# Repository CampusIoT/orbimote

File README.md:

# OrbiMote: open-sourced LoRaWAN high-altitude balloon (HAB) tracker

"urbi et orbi" : to the city and the world

The Orbimote is a LoRa/LoRaWAN endpoint
* for tracking sounding balloons
* and for implementing flying repeaters and flying field testers.

# HW & FW
* [Hardware](./hardware)
* [Firmware](./firmware)

## GNSS additional modules for near-space applications

According [CoCom](https://en.wikipedia.org/wiki/CoCom) regulations, most of commercial GPS modules stop at altitudes higher than 18000 meters and for speeds higher than 1000 knots (1852 km/h).

Here is a list of GPS modules : [gnss_modules.md](./gnss_modules.md)

## Barometers for near-space applications

Here is a list of barometer components and modules : [barometers.md](./barometers.md)

## Flights

[High-altitude flights](https://gricad-gitlab.univ-grenoble-alpes.fr/thingsat/public/-/blob/master/balloons)

### 2019
Valence, May 2019. [more](https://gricad-gitlab.univ-grenoble-alpes.fr/thingsat/public/-/blob/master/balloons/2019-05-09/README.md)

Legend: The balloon track (in red), Orange Liveobject stations (in orange), TTN stations (in grey)
### 2020
Aire-sur-l'Adour, September 2020. [more](https://gricad-gitlab.univ-grenoble-alpes.fr/thingsat/public/-/blob/master/balloons/2020-09-23/README.md)

Legend: The balloon track (in green for departure, blue line and red for arrival), Orange Liveobject stations (in blue)

### 2021
Aire-sur-l'Adour, April 2021. [more](https://gricad-gitlab.univ-grenoble-alpes.fr/thingsat/public/-/blob/master/balloons/2021-04-15/README.md)

Legend: The 3 balloons tracks (in green for departure, red for arrival), Orange Liveobject stations in orange, Requea stations in blue, Swisscom (thru Actility) in red.

## Altenatives
* [HAB2 High Altitude Balloon Tracker RFM9x](https://github.com/StuartsProjects/HAB2)

## Other usages
* Runners trackers
* Meshed-network of trail runners/trekers

## License
TBD

## Authors
* Didier DONSEZ
* Vivien QUEMA
* Gregory NOCERA

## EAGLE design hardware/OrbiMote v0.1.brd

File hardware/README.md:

# OrbiMote :: Hardware  

## Schematics   
* Done with [Eagle 7.7 Express](https://www.autodesk.com/products/eagle/free-download).

## Bill of material

* IMST iM880A
  * MCU: STM32L151CB - 128K FLASH, 10K RAM, Timers, SPI, I2C, USART, USB 2.0 full-speed device/host/OTG controller,DAC, ADC, DMA
  * RADIO: SX1272
* or [IMST iM880B-L](https://wireless-solutions.de/products/radiomodules/im880b-l.html)
* or [IMST iM881A-M](https://wireless-solutions.de/products/long-range-radio/im881a.html)
* MPL3115 : temperature, pressure
* MMA8451 : accelormeter
* MAG3110 : magnetometer
* reed switch
* button
* power switch
* SMA and UFL antenna connectors
* CR2032 battery holder
* plug for AA lithium battery
* pin header for JTAG/SWD
* pin header for RXTX

## Header for JTAG/SWD
Noted as JP1

    Pin 1 : GND
    Pin 2 : VCC
    Pin 3 : JTCK/SWCLK (pin 2 of the iM880a)
    Pin 4 : JTMS/SWDAT (pin 3 of the iM880a)
    Pin 5 : JTDO       (pin 4 of the iM880a)
    Pin 6 : JTDI       (pin 5 of the iM880a)
    Pin 7 : RESET      (pin 7 of the iM880a)

## Header for RXTX
Noted as JP2

    Pin 1 : GND
    Pin 2 : RX
    Pin 3 : TX

## GNSS additional modules for near-space applications

According [CoCom](https://en.wikipedia.org/wiki/CoCom) regulations, most of commercial GPS modules stop at altitudes higher than 18000 meters and for speeds higher than 1000 knots (1852 km/h).

Here is a list of GPS modules : [gnss_modules.md](../gnss_modules.md)

## Barometers for near-space applications

Here is a list of barometer components and modules : [barometers.md](../barometers.md)

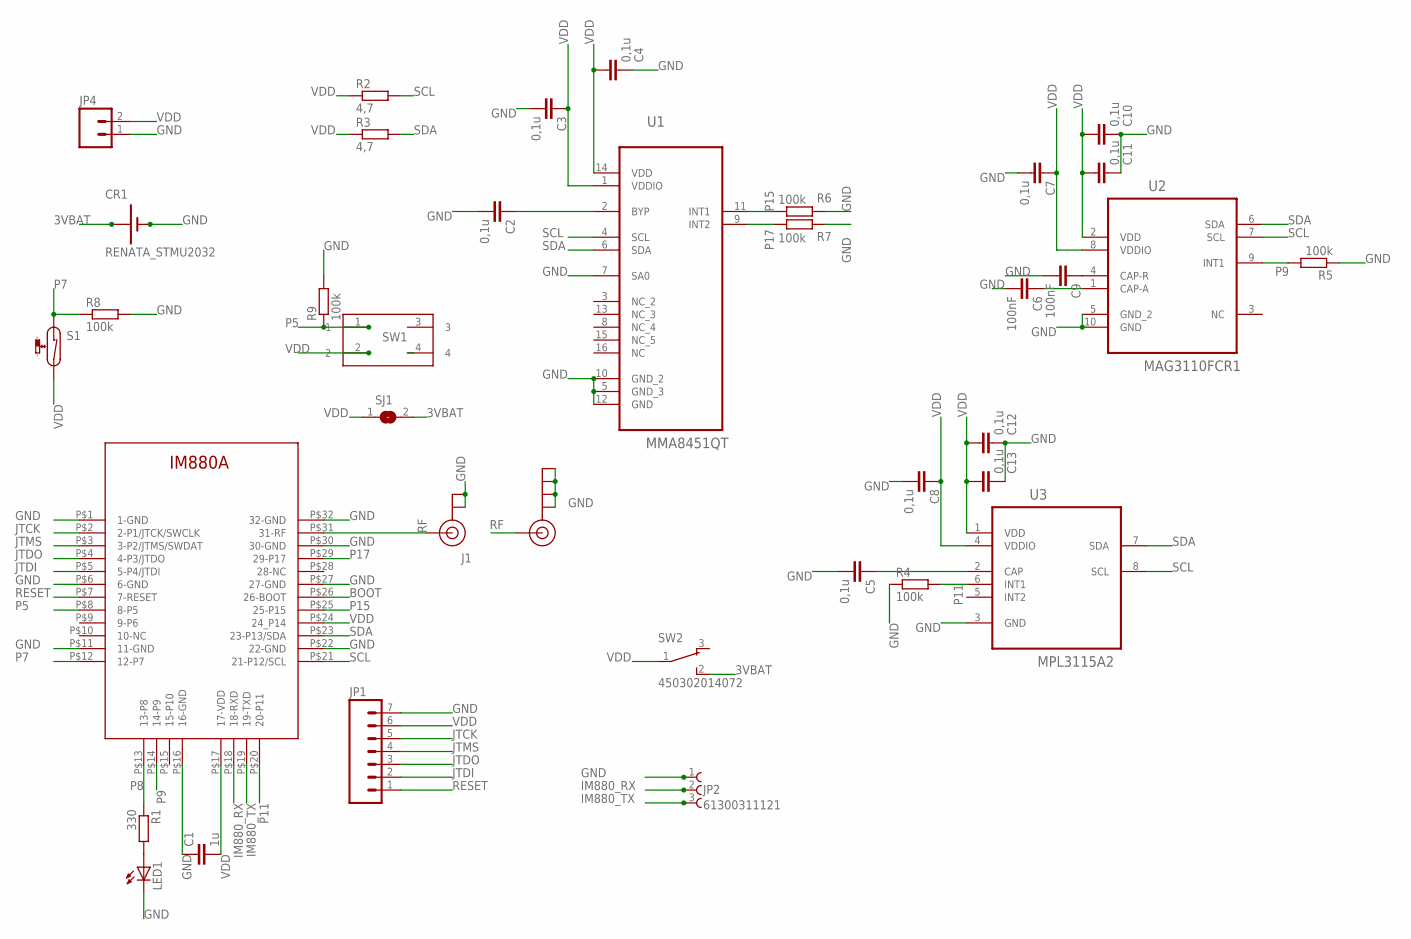
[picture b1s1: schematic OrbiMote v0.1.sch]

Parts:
C1: 1u; C0603
C2, C3, C4, C5, C7, C8, C10, C11, C12, C13: 0,1u; C0603
C6, C9: 100nF; C0603
CR1: RENATA_STMU2032; SMTU2032
IM1: IM880A
J1: U.FL
J$1: SMA_EDGE; SMA-EDGE
JP1: M07; 1X07
JP2: 61300311121
JP4: M02JST-PTH-VERT; JST-2-PTH-VERT
LED1: LEDCHIPLED_0603; CHIPLED_0603
R1: 330; R0603
R2, R3: 4,7; R0603
R4, R5, R6, R7, R8, R9: 100k; R0603
S1: REED-SWITCH-CT10-1530-G1; CT10-G1
SJ1: SJ
SW1: 430152043826
SW2: 450302014072
U1: MMA8451QT; QFN50P300X300X100-16N
U2: MAG3110FCR1; DFN200X200X90-10N
U3: MPL3115A2; DFN300X500X120-8N

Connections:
3VBAT: CR1.+ (3VBAT), SJ1.2, SW2.2
BOOT: IM1.P$26 (26-BOOT)
GND: C1.1, C2.2, C3.2, C4.2, C5.2, C6.2, C7.2, C8.2, C9.2, C10.2, C11.2, C12.2, C13.2, CR1.-, IM1.P$1 (1-GND), IM1.P$6 (6-GND), IM1.P$11 (11-GND), IM1.P$16 (16-GND), IM1.P$22 (22-GND), IM1.P$27 (27-GND), IM1.P$30 (30-GND), IM1.P$32 (32-GND), J1.P$1 (GND), J1.P$2 (GND), J$1.GND@0 (GND), J$1.GND@1 (GND), J$1.GND@2 (GND), J$1.GND@3 (GND), JP1.7, JP2.1, JP4.1, LED1.C, R4.1, R5.1, R6.1, R7.1, R8.2, R9.2, U1.5 (GND_3), U1.7 (SA0), U1.10 (GND_2), U1.12 (GND), U2.5 (GND_2), U2.10 (GND), U3.3 (GND)
IM880_RX: IM1.P$18 (18-RXD), JP2.2
IM880_TX: IM1.P$19 (19-TXD), JP2.3
JTCK: IM1.P$2 (2-P1/JTCK/SWCLK), JP1.5
JTDI: IM1.P$5 (5-P4/JTDI), JP1.2
JTDO: IM1.P$4 (4-P3/JTDO), JP1.3
JTMS: IM1.P$3 (3-P2/JTMS/SWDAT), JP1.4
unnamed: C2.1, U1.2 (BYP)
unnamed: C5.1, U3.2 (CAP)
unnamed: C9.1, U2.4 (CAP-R)
unnamed: C6.1, U2.1 (CAP-A)
unnamed: LED1.A, R1.2
P5: IM1.P$8 (8-P5), R9.1, SW1.1
P7: IM1.P$12 (12-P7), R8.1, S1.1
P8: IM1.P$13 (13-P8), R1.1
P9: IM1.P$14 (14-P9), R5.2, U2.9 (INT1)
P11: IM1.P$20 (20-P11), R4.2, U3.6 (INT1)
P15: IM1.P$25 (25-P15), R6.2, U1.11 (INT1)
P17: IM1.P$29 (29-P17), R7.2, U1.9 (INT2)
RESET: IM1.P$7 (7-RESET), JP1.1
RF: IM1.P$31 (31-RF), J1.P$3 (SIGNAL), J$1.SIG (SIGNAL)
SCL: IM1.P$21 (21-P12/SCL), R2.2, U1.4 (SCL), U2.7 (SCL), U3.8 (SCL)
SDA: IM1.P$23 (23-P13/SDA), R3.2, U1.6 (SDA), U2.6 (SDA), U3.7 (SDA)
VDD: C1.2, C3.1, C4.1, C7.1, C8.1, C10.1, C11.1, C12.1, C13.1, IM1.P$17 (17-VDD), IM1.P$24 (24_P14), JP1.6, JP4.2, R2.1, R3.1, S1.2, SJ1.1, SW1.2, SW2.1, U1.1 (VDDIO), U1.14 (VDD), U2.2 (VDD), U2.8 (VDDIO), U3.1 (VDD), U3.4 (VDDIO)

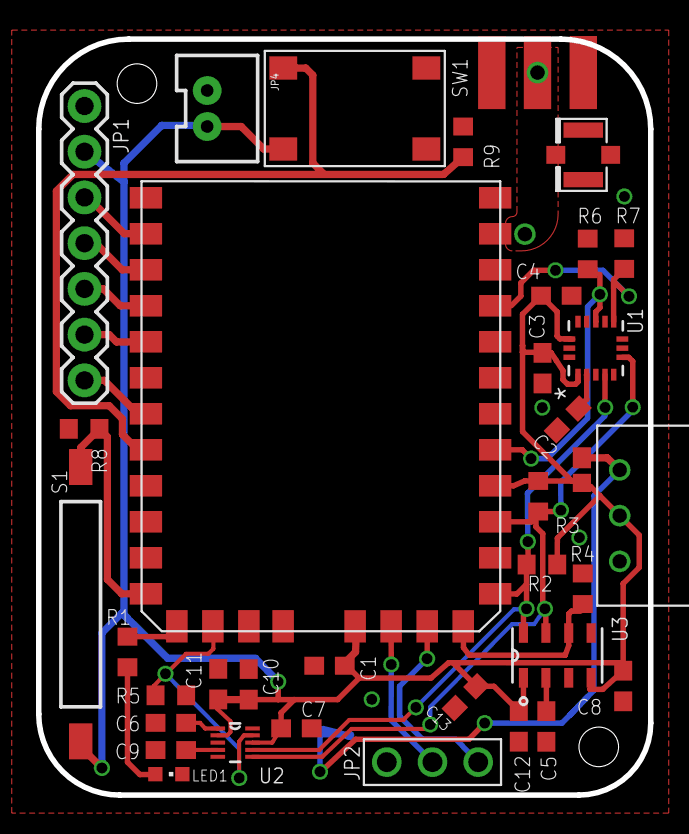
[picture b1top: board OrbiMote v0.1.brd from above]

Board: 2 copper layers, 34.0 x 42.0 mm, 37 parts (1 on the bottom side), 25 nets.

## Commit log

2020-04-03 initial
2020-04-03 add images
2020-04-03 add tab
2020-04-04 add pdf of the design
2020-04-04 add gitignore
2020-04-04 add ref to gnss module
2020-04-09 add initial firmware
2020-04-09 improve doc
2020-04-09 add Header for RXTX
2020-04-10 add barometers.md ref
2020-04-10 add LPS27HHW
2020-04-10 add Amphenol Pressure Sensors
2020-04-10 add more components
2020-10-02 add flight done in September 2020
2020-10-02 add flight done in May 2019
2021-02-05 add field test device firmware
2021-02-05 add missing images
2021-02-05 add RIOT
2021-02-07 add remark
2021-02-17 add todos
2021-02-17 add future fields in uplink payload
2021-02-17 add ref the GNSS module list
2021-02-17 add ST Teseo-LIV3F
2021-02-17 update ST Teseo-LIV3F
2021-02-19 reformat TODO; add utils for base64
2021-02-27 add boards list
2021-02-27 add boards
2021-02-27 add generic node
2021-02-27 add lilyco
2021-03-15 add legends
2021-03-15 add orbimote
2021-03-15 fix url
2021-04-03 add ifndef for baudrate
2021-04-03 add nodered codec
2021-04-03 add watchdog
2021-04-03 improve readme
2021-04-03 avoid quadratic sleep
2021-04-03 improve makefile
2021-04-03 fill buffer with zero
2021-04-03 add tweet
2021-04-04 add example of metadata for benchmark
2021-04-04 fix comment
2021-04-04 add LORAMAC_JOIN_MIN_DATARATE for LLCC68
2021-04-08 improve defines in Makefile
2021-05-06 complete deveui/appeui/appkey settings
2021-05-19 add "see also"
2021-05-27 add 2021 flights
2021-05-27 fix image ref
2021-05-27 add 2021 map
2021-06-18 add authors
2021-06-18 add ref
2021-06-18 fix section title
2021-06-29 fix Quectel L76-L GPS Module
2021-07-16 improvement
2021-07-17 improve Makefile for device customization
2021-07-26 print nwkskey and appskey after otaa join procedure
2021-08-26 add Dragino LGT92
2021-08-26 add components
2021-09-15 add L96
2021-10-13 add define APP_CLOCK_SYNC
2021-10-13 set initial fcnt up (useful for ABP endpoints)
2021-10-25 add Nucleo WL55JC and Nucleo WL55JC2)
2021-10-25 add Air530
2021-10-25 add link to wiki
2022-01-20 add B-L072Z-LRWAN1
2022-03-04 add comment
2022-03-04 fix cast
2022-03-04 fix devaddr print
2022-04-12 add codec for LNS
2022-06-07 add comments
2022-06-07 add missing modules
2022-06-07 add downlinks for rebooting
2022-06-07 remove commit for im880b
2022-06-07 add missing include
2022-06-07 add section for rebooting
2022-06-08 add idosens boards
2022-06-08 add get lorawan network into utils
2022-06-29 add RTK
2022-09-26 add semtech_loramac_set_class in TODO
2023-03-14 add tio for console
2023-06-14 add modules
2023-09-20 add more modules
2023-10-13 add fake remark
2023-10-13 add ZOE-M8Q
2023-10-13 add alt
2023-11-21 add AT6558R
2023-11-28 update and reorg ublox
2024-04-22 add baudrate
2025-05-27 add support for seed_wio-e5
2025-05-27 add todo for i2c scanner
2025-05-27 improve for lora-e5-dev
2026-06-10 add debug trace for APP_CLOCK_SYNC

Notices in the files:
parts and their libraries:
Kurzhubtaster: Copyright: Würth Elektronik
SparkFun-Connectors: Licensing: Creative Commons ShareAlike 4.0 International - https://creativecommons.org/licenses/by-sa/4.0
